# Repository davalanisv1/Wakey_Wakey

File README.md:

# Wakey Wakey!

Wakey Wakey! Is a blare alarm made by David Alanis to complete the "Blare!" Mission from the Stardance Challenge, it was fun, and helped me learn PCB design through KiCad.

## Components Used:
- 1x Seeed XIAO ESP32C3
- 4x MX-Style Keyboard Switches
- 4x White Blank DSA Keycaps
- 4x Through-Hole 1N4148 Diodes
- 1x 2.25in TFT Screen
- 1x 3.3V Piezo Buzzer
- 1x 2.54mm 8 Pin Male Header
- 8x 20cm Female-Female Jumper Wires
- 8x M3x5x4 Heatset Inserts
- 4x M3x8mm Screws
- 4x M3x16mm Screws

## Schematic:

## 3D PCB Viewer:

## Clock Design:

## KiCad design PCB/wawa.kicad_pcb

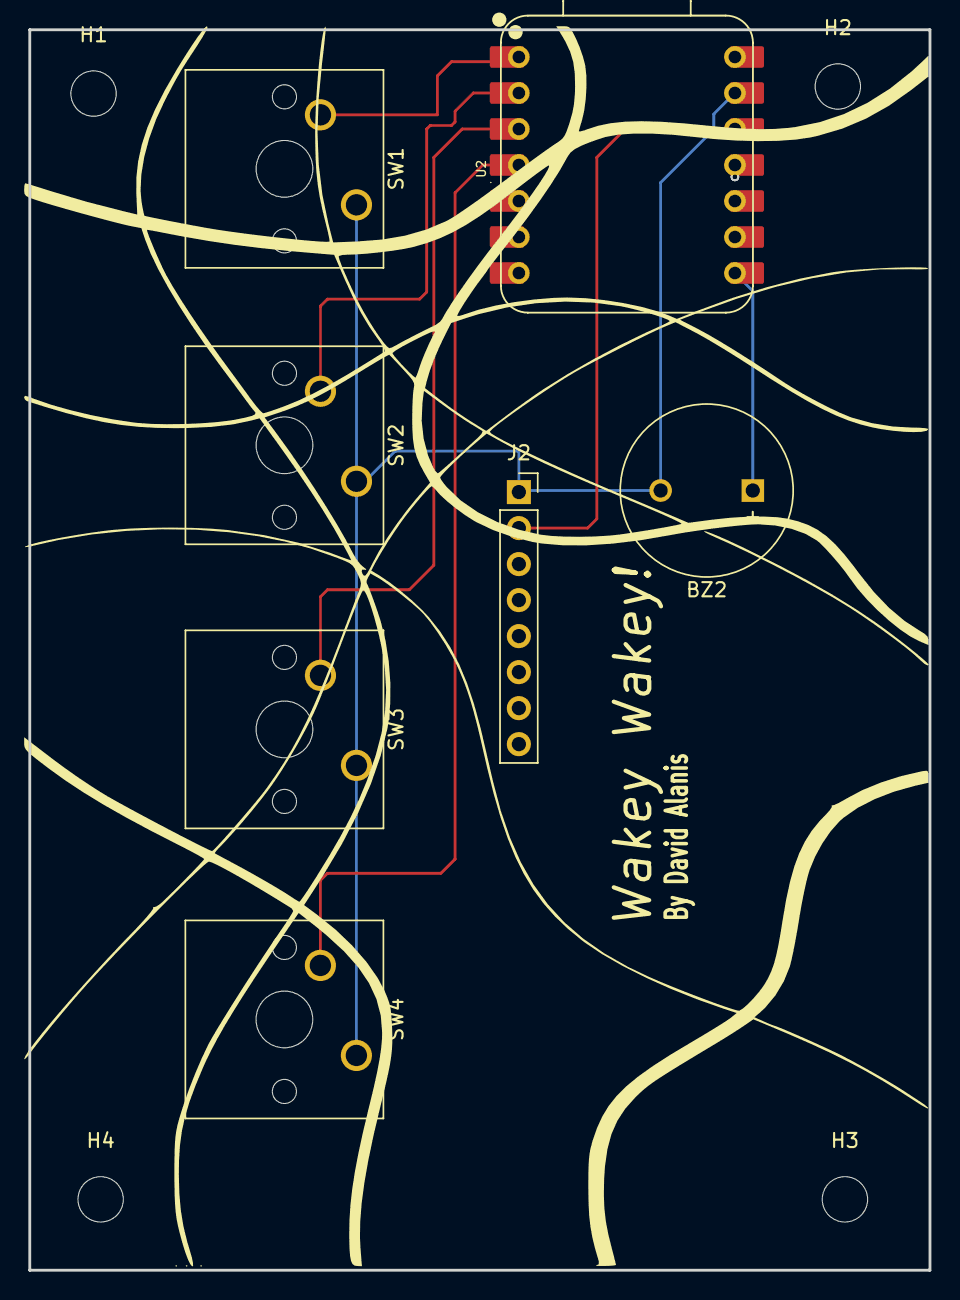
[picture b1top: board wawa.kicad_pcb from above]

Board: 2 copper layers, 63.5 x 87.5 mm, 11 parts (0 on the bottom side), 7 nets.

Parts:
BZ2: Buzzer; MagneticBuzzer_ProSignal_ABT-410-RC
H1, H2, H3, H4: MountingHole; MountingHole_3.2mm_M3
J2: Conn_01x08_Pin; PinSocket_1x08_P2.54mm_Vertical
SW1, SW2, SW3, SW4: SW_Push; SW_Cherry_MX_1.00u_PCB
U2: XIAO-ESP32-C3-SMD; XIAO-ESP32-C3-DIP

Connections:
+3.3V: J2.2, U2.12 (3V3_OUT)
GND: BZ2.2 (-), J2.1, SW1.1, SW2.1, SW3.1, SW4.1, U2.13 (GND)
unnamed: BZ2.1 (+), U2.8 (D7)
unnamed: SW1.2, U2.1 (D0)
unnamed: SW2.2, U2.2 (D1)
unnamed: SW3.2, U2.3 (D2)
unnamed: SW4.2, U2.4 (D3)
